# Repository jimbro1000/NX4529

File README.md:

# MC14529 Replacement #

This repository contains the design for a CPLD based
replacement for the long obsolete MC14529 analog
multiplexer. The design is intended only to act as a
substitute in the Dragon 32/64 computers.

## Limitations ##

The current implementation is functionally complete but
there is an idiosyncracy of the controlling CPLD that
needs to be noted. At startup all control outputs are
floating until each ones goes into a high (on) state,
the result is that the route of any switch will non-
deterministic until positively switched.

## Design ##

The design is based around the Renesas SLG46824 CPLD.
This is a 3mm x 2mm device (about the size of a 1/4W
leaded resistor). The CPLD reproduces the truth table
of the original device.

The actual multiplexing is performed by an array of
LS74LVC1G3157 analog SPDT switches. These are available
in very small (1mm x 1mm) packages allowing eight of them 
to be fitted in the available space.

The output inhibit is performed by two more SPST
switches.

The board design retains the footprint of a DIP-16
component. To necessitate compliance with the available
space the PCB is 6-layer and utilises minimum sized vias
and routing. This may limit signal fidelity. Where possible
signal routing is increased in width and is kept separate 
from control routing.

## License ##

This project is licensed under creative commons CC-BY-SA 4.0

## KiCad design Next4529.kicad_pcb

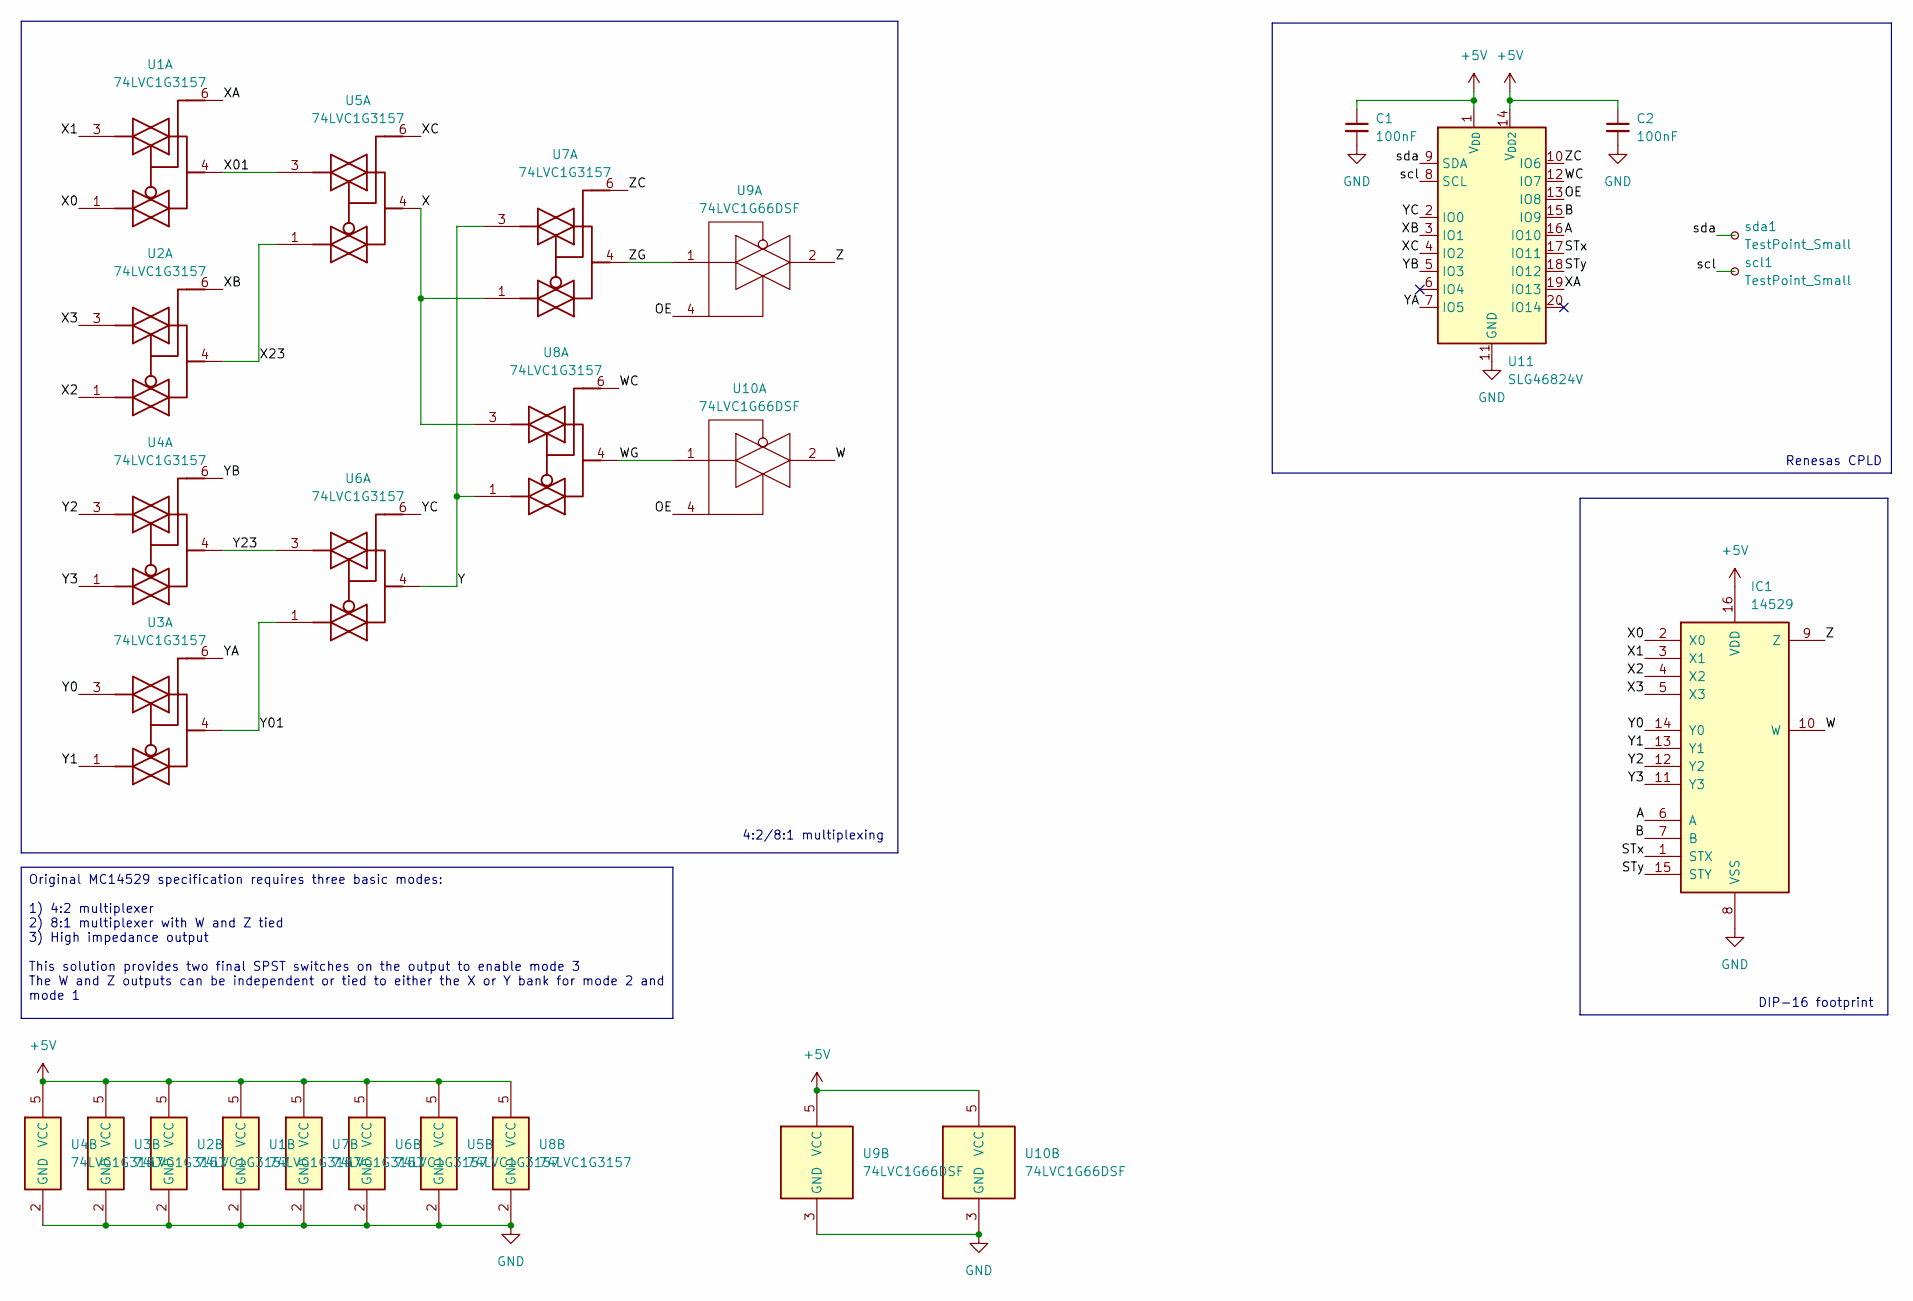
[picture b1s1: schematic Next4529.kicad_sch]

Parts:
C1, C2: 100nF; C_0402_1005Metric; DigiKey 1276-CL05B104KP5VPNCCT-ND
IC1: 14529; DIP-16_board
U1, U2, U3, U4, U5, U6, U7, U8: 74LVC1G3157; Texas_USON-6_1x1.45mm_P0.5mm_SMD; DigiKey 296-14909-1-ND
U9, U10: 74LVC1G66DSF; Texas_USON-6_1x1.45mm_P0.5mm_SMD
U11: SLG46824V; Renesas_UQFN-20_2x3mm_P0.4mm_LayoutBorder4x6y; DigiKey 1695-SLG46824VCT-ND
scl1: TestPoint_Small; TestPoint_Pad_D1.0mm
sda1: TestPoint_Small; TestPoint_Pad_D1.0mm

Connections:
+5V: C1.1, C2.1, IC1.16 (VDD), U1.5 (VCC), U2.5 (VCC), U3.5 (VCC), U4.5 (VCC), U5.5 (VCC), U6.5 (VCC), U7.5 (VCC), U8.5 (VCC), U9.5 (VCC), U10.5 (VCC), U11.1 (V_{DD}), U11.14 (V_{DD2})
/A: IC1.6 (A), U11.16 (IO10)
/B: IC1.7 (B), U11.15 (IO9)
/OE: U9.4, U10.4, U11.13 (IO8)
/STx: IC1.1 (STX), U11.17 (IO11)
/STy: IC1.15 (STY), U11.18 (IO12)
/W: IC1.10 (W), U10.2
/WC: U8.6, U11.12 (IO7)
/WG: U8.4, U10.1
/X: U5.4, U7.1, U8.3
/X0: IC1.2 (X0), U1.1
/X1: IC1.3 (X1), U1.3
/X01: U1.4, U5.3
/X2: IC1.4 (X2), U2.1
/X3: IC1.5 (X3), U2.3
/X23: U2.4, U5.1
/XA: U1.6, U11.19 (IO13)
/XB: U2.6, U11.3 (IO1)
/XC: U5.6, U11.4 (IO2)
/Y: U6.4, U7.3, U8.1
/Y0: IC1.14 (Y0), U3.3
/Y1: IC1.13 (Y1), U3.1
/Y01: U3.4, U6.1
/Y2: IC1.12 (Y2), U4.3
/Y3: IC1.11 (Y3), U4.1
/Y23: U4.4, U6.3
/YA: U3.6, U11.7 (IO5)
/YB: U4.6, U11.5 (IO3)
/YC: U6.6, U11.2 (IO0)
/Z: IC1.9 (Z), U9.2
/ZC: U7.6, U11.10 (IO6)
/ZG: U7.4, U9.1
/scl: U11.8 (SCL), scl1.1
/sda: U11.9 (SDA), sda1.1
GND: C1.2, C2.2, IC1.8 (VSS), U1.2 (GND), U2.2 (GND), U3.2 (GND), U4.2 (GND), U5.2 (GND), U6.2 (GND), U7.2 (GND), U8.2 (GND), U9.3 (GND), U10.3 (GND), U11.11 (GND)

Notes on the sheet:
Renesas CPLD
DIP-16 footprint
4:2/8:1 multiplexing
Original MC14529 specification requires three basic modes: 1) 4:2 multiplexer 2) 8:1 multiplexer with W and Z tied 3) High impedance output This solution provides two final SPST switches on the output to enable mode 3 The W and Z outputs can be independent or tied to either the X or Y bank for mode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

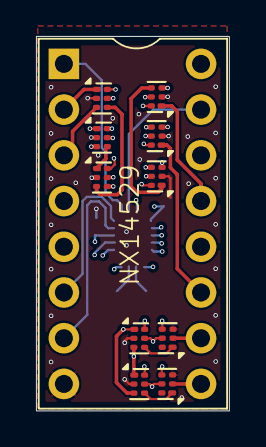
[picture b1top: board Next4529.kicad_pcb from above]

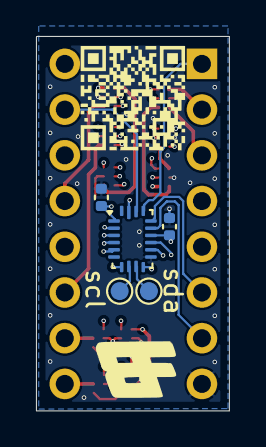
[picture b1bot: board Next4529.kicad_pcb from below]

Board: 6 copper layers, 10.7 x 20.8 mm, 17 parts (6 on the bottom side), 35 nets.

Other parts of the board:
QR*****: https://github.com/jimbro1000/NX4529; ProjectQR

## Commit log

2025-11-18 add notes to schematic
2025-11-18 redesign
2025-11-20 refine routing
